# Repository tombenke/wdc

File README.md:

# wdc
Weather Data Collector

Run the NATS server in docker:

```bash
    docker run -it --rm --network=host -p 4222:4222 -p 6222:6222 -p 8222:8222 --name nats-main nats
```

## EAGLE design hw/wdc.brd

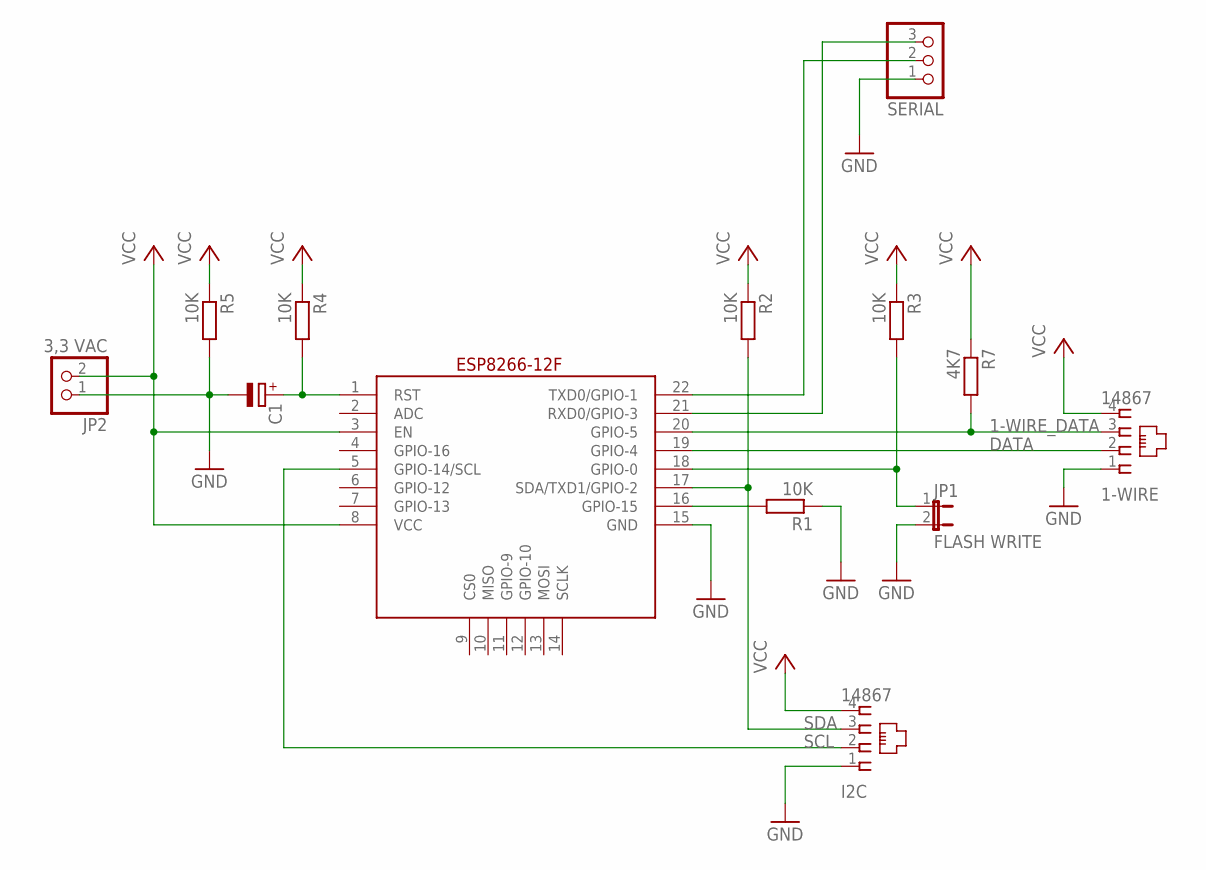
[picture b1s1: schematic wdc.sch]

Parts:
1-WIRE: 14867
C1: CPOL-EUE2-5; E2-5
I2C: 14867
JP1: FLASH WRITE; JP1
JP2: 3,3 VAC; 1X02
R1, R2, R3, R4, R5: 10K; 0204/7
R7: 4K7; 0204/7
SERIAL: PINHD-1X3; 1X03
U$1: ESP826612F

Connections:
1-WIRE_DATA: 1-WIRE.3, R7.2, U$1.20 (GPIO-5)
DATA: 1-WIRE.2, U$1.19 (GPIO-4)
GND: 1-WIRE.1, C1.-, I2C.1, JP1.2, JP2.1, R1.1, R5.2, SERIAL.1, U$1.15 (GND)
unnamed: R1.2, U$1.16 (GPIO-15)
unnamed: JP1.1, R3.2, U$1.18 (GPIO-0)
unnamed: C1.+, R4.2, U$1.1 (RST)
unnamed: SERIAL.2, U$1.22 (TXD0/GPIO-1)
unnamed: SERIAL.3, U$1.21 (RXD0/GPIO-3)
SCL: I2C.2, U$1.5 (GPIO-14/SCL)
SDA: I2C.3, R2.2, U$1.17 (SDA/TXD1/GPIO-2)
VCC: 1-WIRE.4, I2C.4, JP2.2, R2.1, R3.1, R4.1, R5.1, R7.1, U$1.3 (EN), U$1.8 (VCC)

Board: 2 copper layers, 13 parts (0 on the bottom side), 11 nets, no tracks yet.

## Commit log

2018-01-05 Add hardware schematics of wdc circuit
2018-01-05 Add firmware of wdc
2018-01-06 Add NATS docker start info to README Change temperature report message format Add deviceTemp sensor
2018-01-07 Add natsCmd.js to send commands to the sensors through NATS Add wds.js to subscribe and log messages sent by the sensors through NATS Set temp sensor resolution during startup Change NATS server conf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
